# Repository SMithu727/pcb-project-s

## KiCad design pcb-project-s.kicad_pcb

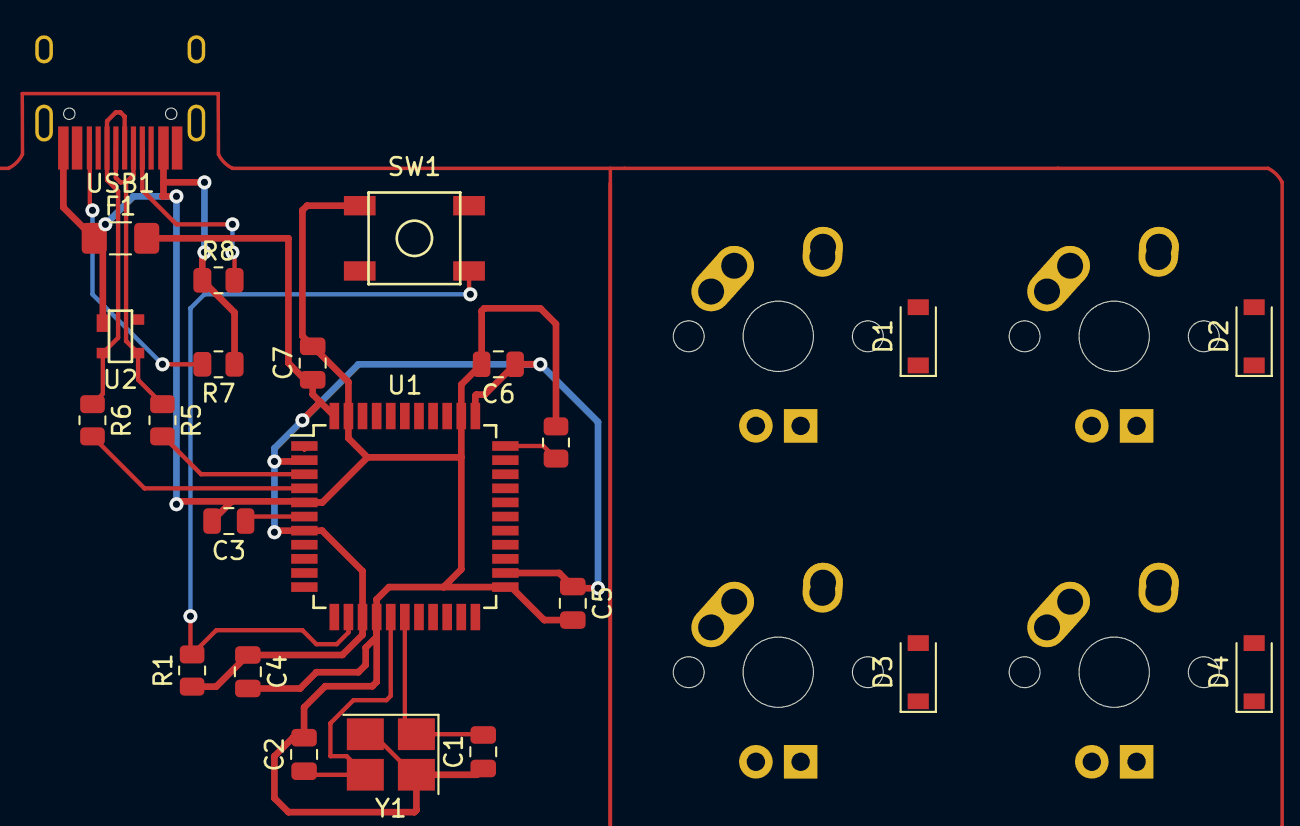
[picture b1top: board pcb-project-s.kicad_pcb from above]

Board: 2 copper layers, 27 parts (0 on the bottom side), 21 nets.

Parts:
C1, C2: 22pF; C_0805_2012Metric
C3: 1uF; C_0805_2012Metric
C4, C5, C6: 0.1uF; C_0805_2012Metric
C7: 10uF; C_0805_2012Metric
D1, D2, D3, D4: D_Small; D_SOD-123
F1: 500m; Fuse_1206_3216Metric_Pad1.42x1.75mm_HandSolder
MX1, MX2, MX3, MX4: MX-LED; MX-1U
R1, R4: 10k; R_0805_2012Metric
R5, R6: 22; R_0805_2012Metric
R7, R8: 5.1k; R_0805_2012Metric
SW1: SW_Push; SKQG-1155865
U1: ATmega32U4-A; TQFP-44_10x10mm_P0.8mm
U2: PRTR5V0U2X; SOT143B
USB1: HRO-TYPE-C-31-M-12; HRO-TYPE-C-31-M-12-HandSoldering
Y1: 16MHz; Crystal_SMD_3225-4Pin_3.2x2.5mm_HandSoldering

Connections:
+5V: C4.1, C5.1, C6.1, C7.1, F1.2, R1.1, U1.2 (UVCC), U1.7 (VBUS), U1.14 (VCC), U1.24 (AVCC), U1.34 (VCC), U1.44 (AVCC)
/COL0: MX1.1 (COL), MX2.1 (COL)
/COL1: MX3.1 (COL), MX4.1 (COL)
/ROW0: D1.1 (K), D2.1 (K)
/ROW1: D3.1 (K), D4.1 (K)
GND: C1.1, C2.2, C3.2, C4.2, C5.2, C6.2, C7.2, F1.1, R4.2, R7.1, R8.1, SW1.1, U1.5 (UGND), U1.15 (GND), U1.23 (GND), U1.35 (GND), U1.43 (GND), U2.1 (GND), USB1.2 (VBUS), USB1.12 (GND), USB1.13 (SHIELD), Y1.2, Y1.4
unnamed: C1.2, U1.17 (XTAL1), Y1.1
unnamed: C2.1, U1.16 (XTAL2), Y1.3
unnamed: C3.1, U1.6 (UCAP)
unnamed: D1.2 (A), MX1.2 (ROW)
unnamed: D2.2 (A), MX3.2 (ROW)
unnamed: D3.2 (A), MX2.2 (ROW)
unnamed: D4.2 (A), MX4.2 (ROW)
unnamed: R1.2, SW1.2, U1.13 (~RESET)
unnamed: R4.1, U1.33 (~HWB/PE2)
unnamed: R5.1, U2.3 (IO2), USB1.5 (DN2), USB1.7 (DN1)
unnamed: R5.2, U1.3 (D-)
unnamed: R6.1, U2.2 (IO1), USB1.6 (DP1), USB1.8 (DP2)
unnamed: R6.2, U1.4 (D+)
unnamed: R7.2, USB1.10 (CC2)
unnamed: R8.2, USB1.4 (CC1)

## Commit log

2022-08-24 Created KiCad Project
2022-08-24 Added submodules, libaries
2022-08-24 Assigning Footprints
2022-08-25 Designed the PCB
